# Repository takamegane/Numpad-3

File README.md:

# Numpad-3
 
## 必要なパーツ
* RP2040 zero x1  
* 1N4148W SMDダイオード x22  
* kailh スイッチソケット(MX用) x19-22  
* 2Uスタビライザー x1  
* cherry MX互換キースイッチ x19-22  
* EC12互換ロータリーエンコーダ x0-3  
* キーキャップ  
* ネオジム磁石 6mm x 3mm x12  
* ポロンスポンジ  
* USB Type-cケーブル x1

## ケースについて
ポロンスポンジを用いたガスケットマウント方式です。  
固定はネオジム磁石で上下のケースを固定しています。 
入手先としてはダイソーで販売がありますのでそちらを購入いただくとよいと思います。

超強力マグネットミニ ８コ入
https://jp.daisonet.com/products/4549131156621
ネオジム磁石はケース接着剤で固定してください。接着剤は少な目で十分です。
一部ハマりにくいところがあるかもしれませんが、やすりで広げるか力を入れればはめ混むことが出来ます。

またガスケットパーツのポロンスポンジは以下で入手出来ます。

Keebox Poron Gasket Strip 32 Gaskets 3mm
https://a.aliexpress.com/_ooY0SvX
こちらは加工不要で貼り付けるだけで使用できます。

もしくはamazon等で販売されている以下のスポンジを加工して貼り付けることで代用可能です。
イノアック ポロンスポンジロール 3tX100mmX1M テープ付 黒 L24-3100MT
https://amzn.asia/d/iE0oSrb
こちらは30mmx3mm程度に切ってスイッチプレートのガスケット部分の両側に貼り付けてください。

## はんだ付けについて
一般的な自作キーボードと作業は同じです。
RP2040 zeroのみ裏表の注意が必要です。
以下のような向きではんだ付けを行ってください。
基板表側にブートスイッチ、リセットスイッチが来る向きで、実装基板の裏側に取り付けます。

## ファームウェアについて
vialでキーマップを変更できます。基本的なファームとなっているため、好みに合わせてキーマップを作成しなおしてください。

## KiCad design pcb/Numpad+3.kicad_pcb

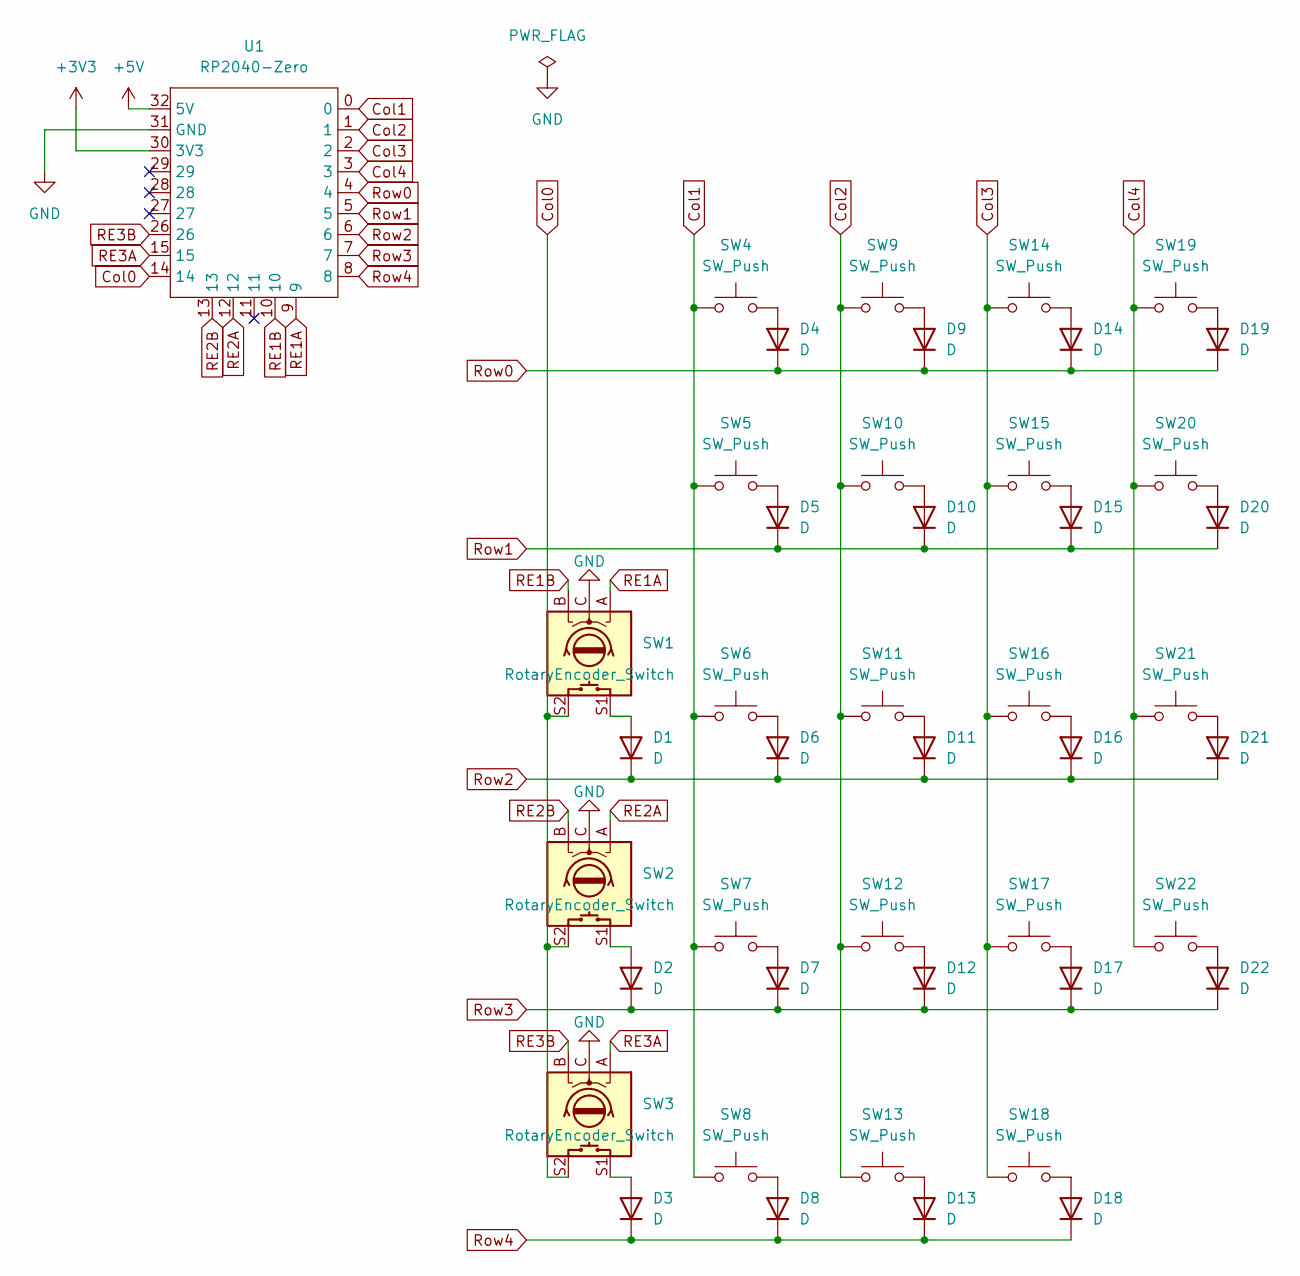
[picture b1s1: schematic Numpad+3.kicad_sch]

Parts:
D1, D2, D3, D4, D5, D6, D7, D8, D9, D10, D11, D12, D13, D14, D15, D16, D17, D18, D19, D20, D21, D22: D; Diode_SMD
SW1, SW2, SW3: RotaryEncoder_Switch; MX1U_Hotswap+RE
SW4, SW5, SW6, SW7, SW8, SW9, SW10, SW11, SW12, SW13, SW14, SW15, SW16, SW17, SW18, SW19, SW20, SW21: SW_Push; MX1U_Hotswap
SW22: SW_Push; MX2U_Hotswap
U1: RP2040-Zero; RP2040 Zero_fix

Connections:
+3V3: U1.30 (3V3)
+5V: U1.32 (5V)
Col0: SW1.S2, SW2.S2, SW3.S2, U1.14
Col1: SW4.1, SW5.1, SW6.1, SW7.1, SW8.1, U1.0
Col2: SW9.1, SW10.1, SW11.1, SW12.1, SW13.1, U1.1
Col3: SW14.1, SW15.1, SW16.1, SW17.1, SW18.1, U1.2
Col4: SW19.1, SW20.1, SW21.1, SW22.1, U1.3
GND: SW1.C, SW2.C, SW3.C, U1.31 (GND)
unnamed: D1.2 (A), SW1.S1
unnamed: D2.2 (A), SW2.S1
unnamed: D3.2 (A), SW3.S1
unnamed: D4.2 (A), SW4.2
unnamed: D5.2 (A), SW5.2
unnamed: D6.2 (A), SW6.2
unnamed: D7.2 (A), SW7.2
unnamed: D8.2 (A), SW8.2
unnamed: D9.2 (A), SW9.2
unnamed: D10.2 (A), SW10.2
unnamed: D11.2 (A), SW11.2
unnamed: D12.2 (A), SW12.2
unnamed: D13.2 (A), SW13.2
unnamed: D14.2 (A), SW14.2
unnamed: D15.2 (A), SW15.2
unnamed: D16.2 (A), SW16.2
unnamed: D17.2 (A), SW17.2
unnamed: D18.2 (A), SW18.2
unnamed: D19.2 (A), SW19.2
unnamed: D20.2 (A), SW20.2
unnamed: D21.2 (A), SW21.2
unnamed: D22.2 (A), SW22.2
RE1A: SW1.A, U1.9
RE1B: SW1.B, U1.10
RE2A: SW2.A, U1.12
RE2B: SW2.B, U1.13
RE3A: SW3.A, U1.15
RE3B: SW3.B, U1.26
Row0: D4.1 (K), D9.1 (K), D14.1 (K), D19.1 (K), U1.4
Row1: D5.1 (K), D10.1 (K), D15.1 (K), D20.1 (K), U1.5
Row2: D1.1 (K), D6.1 (K), D11.1 (K), D16.1 (K), D21.1 (K), U1.6
Row3: D2.1 (K), D7.1 (K), D12.1 (K), D17.1 (K), D22.1 (K), U1.7
Row4: D3.1 (K), D8.1 (K), D13.1 (K), D18.1 (K), U1.8

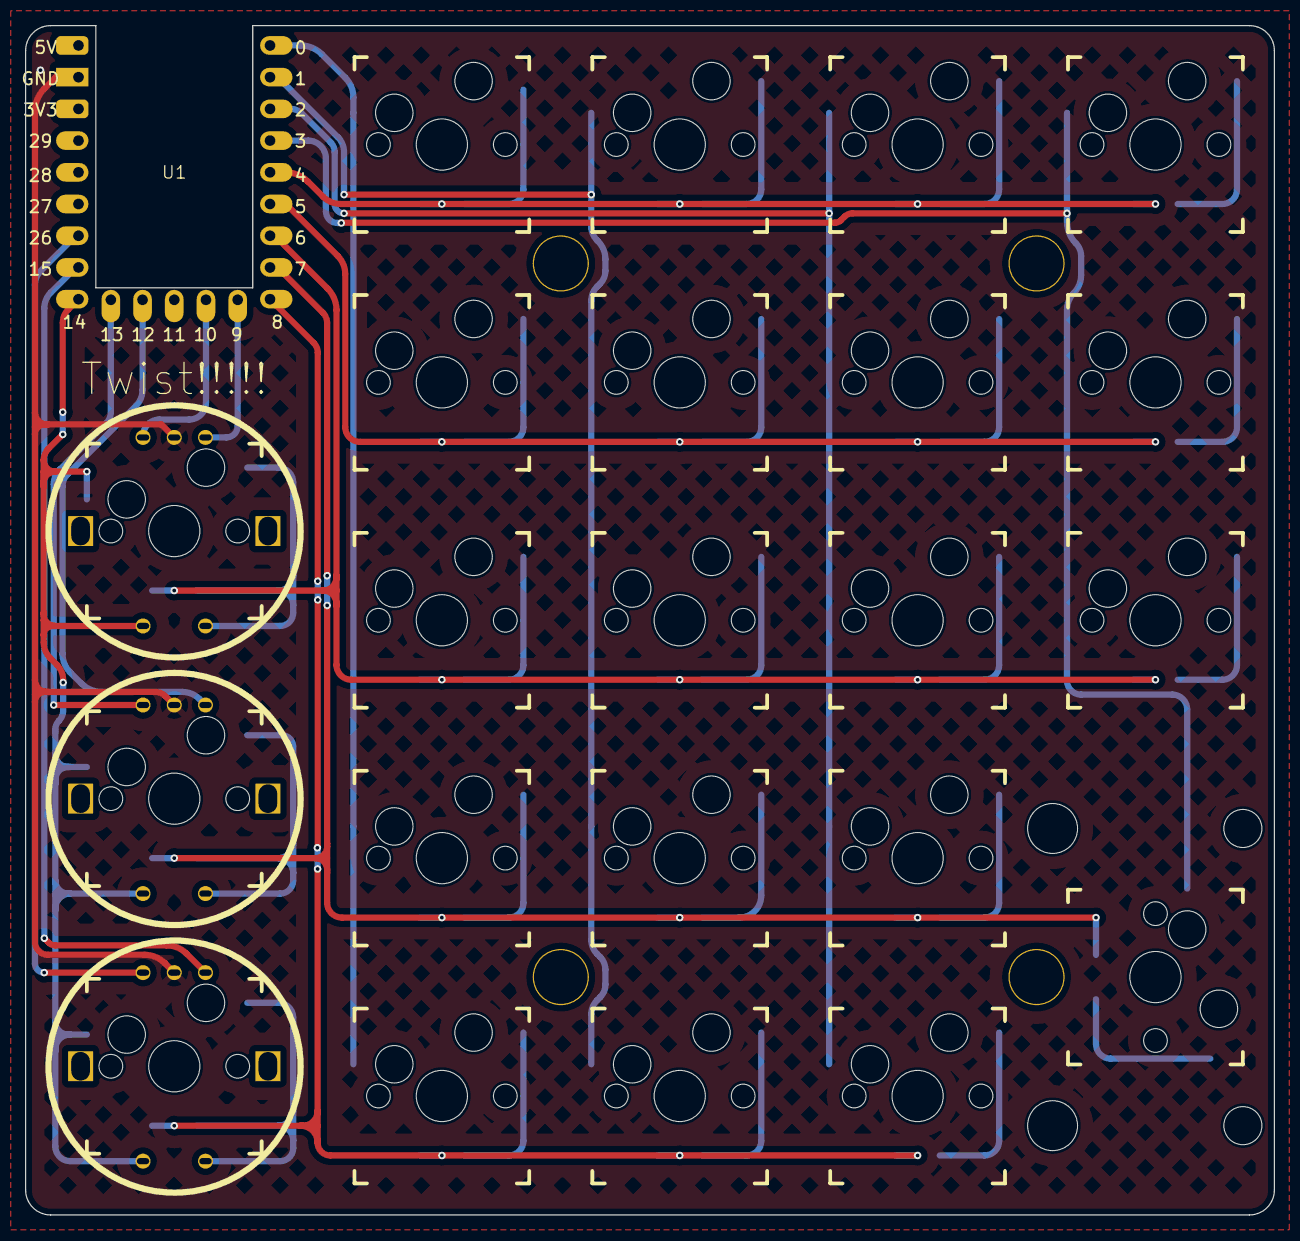
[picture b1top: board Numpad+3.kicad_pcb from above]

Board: 2 copper layers, 100.0 x 95.2 mm, 49 parts (0 on the bottom side), 39 nets.

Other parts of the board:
Ref**: Val**; m2_Spacer_Hole
Ref**#2, Ref**#3, Ref**#4: Val**; m2_Spacer_Hole

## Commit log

2025-05-01 add file
2025-05-02 addjpg
2025-05-04 add firmware data
2025-07-28 ロック解除位置変更
    記述ミスの修正
